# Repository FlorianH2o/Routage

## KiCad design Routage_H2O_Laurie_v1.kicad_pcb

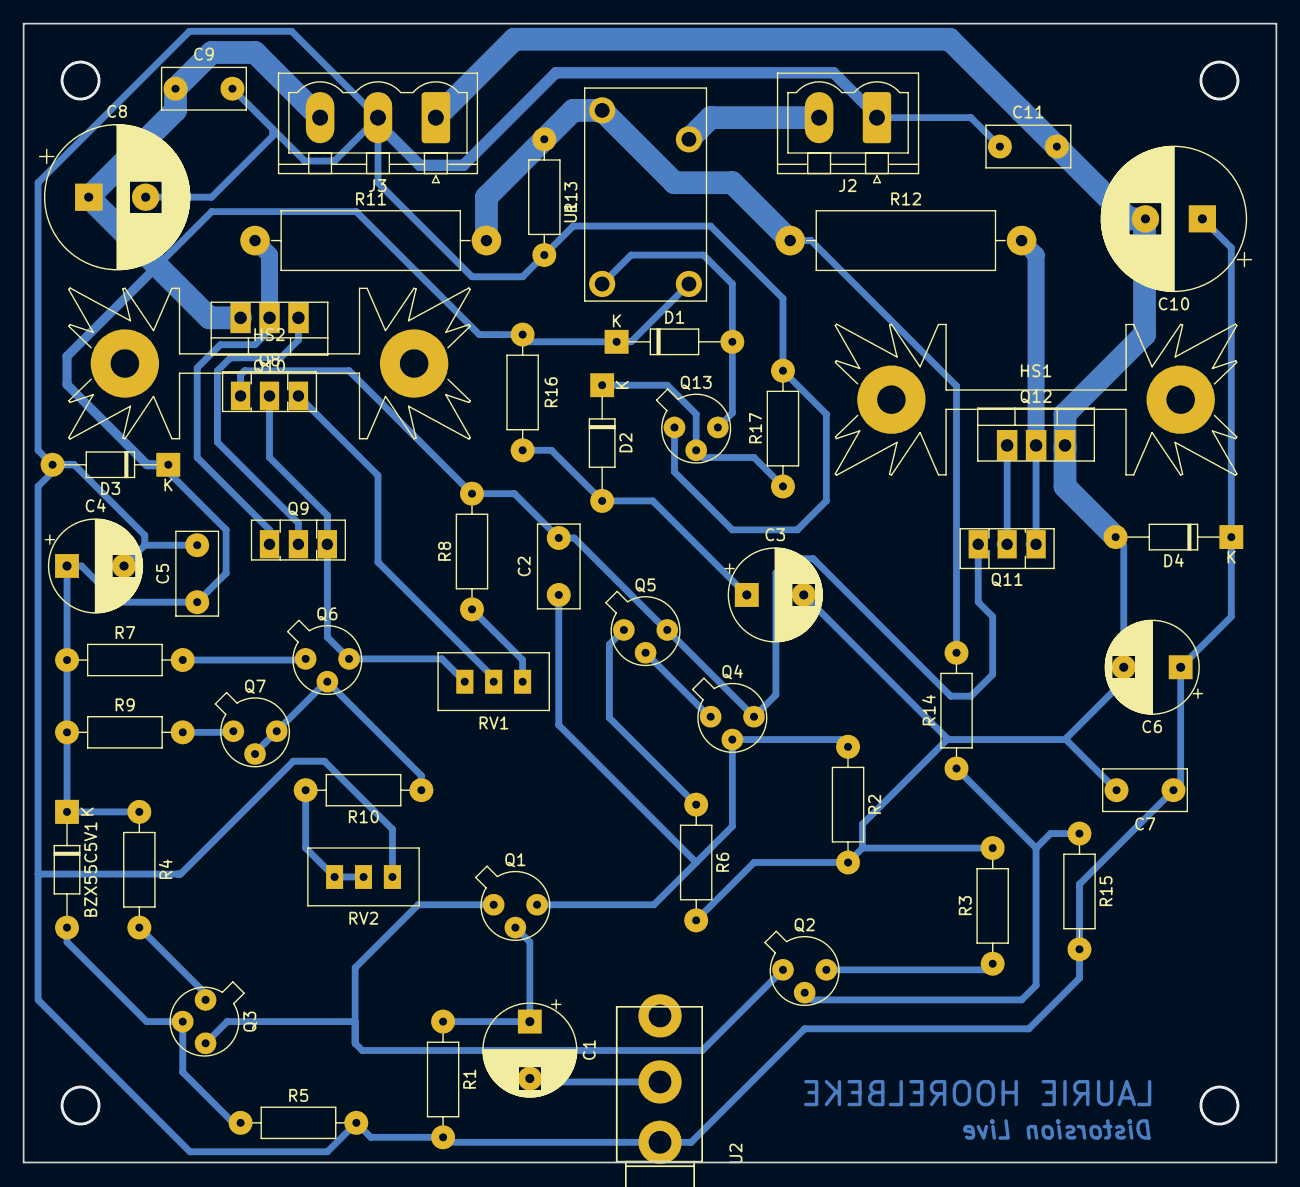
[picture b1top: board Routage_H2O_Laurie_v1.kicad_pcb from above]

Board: 2 copper layers, 110.0 x 100.0 mm, 54 parts (0 on the bottom side), 30 nets.

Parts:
BZX55C5V1: Dz1; D_DO-35_SOD27_P10.16mm_Horizontal
C1, C3: 47u; CP_Radial_D8.0mm_P5.00mm
C2: C; C_Rect_L7.2mm_W3.5mm_P5.00mm_FKS2_FKP2_MKS2_MKP2
C4, C6: 10u; CP_Radial_D8.0mm_P5.00mm
C5, C7, C9, C11: 100n; C_Rect_L7.2mm_W3.5mm_P5.00mm_FKS2_FKP2_MKS2_MKP2
C8, C10: 470u; CP_Radial_D12.5mm_P5.00mm
D1, D2: 1N4148; D_DO-35_SOD27_P10.16mm_Horizontal
D3, D4: 1N4001; D_DO-35_SOD27_P10.16mm_Horizontal
HS1, HS2: Heatsink; Heatsink_Fischer_SK104-STC-STIC_35x13mm_2xDrill2.5mm
J2: Conn_01x02; PhoenixContact_MSTBVA_2,5_2-G-5,08_1x02_P5.08mm_Vertical
J3: Conn_01x03; PhoenixContact_MSTBVA_2,5_3-G-5,08_1x03_P5.08mm_Vertical
Q1, Q2, Q3, Q6, Q7: 2N2907; TO-18-3
Q4, Q5, Q13: 2N2222; TO-18-3
Q8, Q9: BD139; TO-126-3_Vertical
Q10: TIP32; TO-220-3_Vertical
Q11: BD138; TO-126-3_Vertical
Q12: TIP31; TO-220-3_Vertical
R1, R2, R3, R4, R5, R6, R7, R8, R9, R10, R13, R14, R15, R16, R17: R; R_Axial_DIN0207_L6.3mm_D2.5mm_P10.16mm_Horizontal
R11, R12: R; R_Axial_DIN0516_L15.5mm_D5.0mm_P20.32mm_Horizontal
RV1, RV2: R_POT; Potentiometer_Bourns_3296W_Vertical
U1: Relay_1CT; RELAIS_1CT-4
U2: Jack_Mono; Jack_35RAPC2AV

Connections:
+12V: BZX55C5V1.1, C4.1, C5.1, C8.1, C9.1, D1.1, D3.1, J3.3, Q10.3, R4.1, R7.1, R9.1, R16.1, U1.b2
-12V: C3.2, C6.2, C7.2, C10.2, C11.2, D4.2, J3.1, Q12.3, R2.2, R3.2, R6.2
GND: C4.2, C5.2, C6.1, C7.1, C8.2, C9.2, C10.1, C11.1, D3.2, D4.1, J2.1, J3.2, Q13.1, R1.2, R5.2, R13.2, R15.2, R17.2, RV2.3, U2.G
unnamed: BZX55C5V1.2, Q3.2, R5.1
unnamed: C1.1, Q1.2, R1.1
unnamed: C1.2, U2.T
unnamed: C2.1, Q1.3, Q4.2, R2.1
unnamed: C2.2, Q4.3, Q5.3, Q8.1, Q11.3, R8.2
unnamed: C3.1, D2.2, R16.2
unnamed: D1.2, Q13.3, U1.b1
unnamed: D2.1, Q13.2, R17.1
unnamed: J2.2, U1.c2
unnamed: Q1.1, Q2.1, Q3.3
unnamed: Q2.2, R14.1, R15.1
unnamed: Q2.3, R3.1
unnamed: Q3.1, R4.2
unnamed: Q4.1, Q5.2
unnamed: Q5.1, R6.1
unnamed: Q6.1, R7.2
unnamed: Q6.2, Q7.2, Q7.3, R10.1
unnamed: Q6.3, Q8.2, Q9.3, RV1.1
unnamed: Q7.1, R9.2
unnamed: Q8.3, RV1.2
unnamed: Q9.2, Q10.1
unnamed: Q9.1, Q10.2, R11.1
unnamed: Q11.1, Q12.2, R12.2
unnamed: Q11.2, Q12.1
unnamed: R8.1, RV1.3
unnamed: R10.2, RV2.1, RV2.2
unnamed: R11.2, R12.1, R13.1, R14.2, U1.c1

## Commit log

2021-04-11 projetbase
2021-04-11 empreinteupdate
2021-04-11 crashtest
2021-04-11 pcb1
2021-04-11 PlacementFinito
2021-04-17 Routagefinal
